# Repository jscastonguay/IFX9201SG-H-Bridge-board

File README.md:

# IFX9201SG-H-Bridge-board
HB board based on IFX9201SG IC.

This board is the replacement part of PmodHB5. This is why it follows the same interfaces

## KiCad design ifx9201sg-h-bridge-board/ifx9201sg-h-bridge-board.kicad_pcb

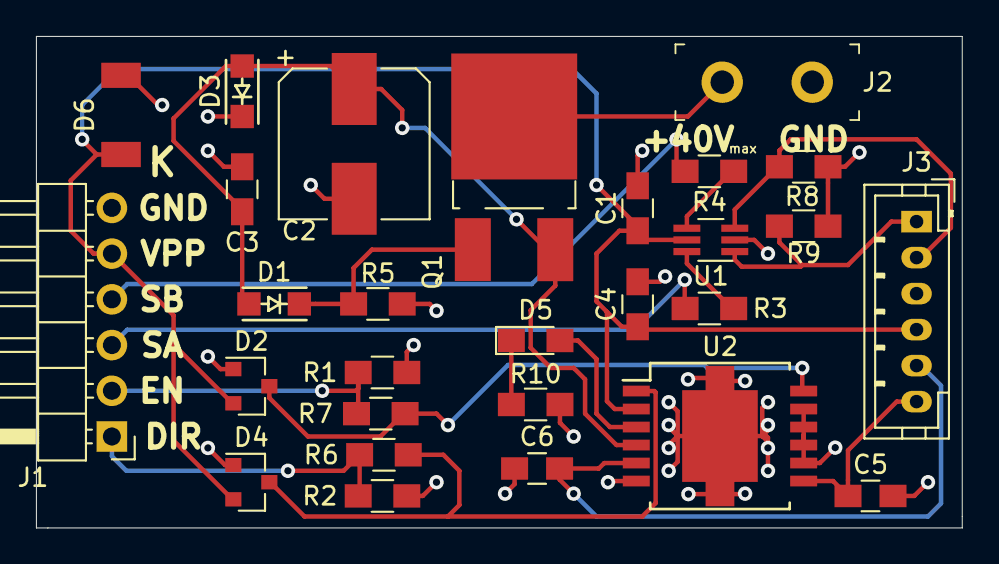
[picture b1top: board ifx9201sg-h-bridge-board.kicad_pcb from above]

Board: 2 copper layers, 51.4 x 27.3 mm, 28 parts (0 on the bottom side), 19 nets.

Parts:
C1, C3, C4: 0.1u; C_0805_HandSoldering
C2: 100u; CP_Elec_8x10
C5, C6: 10n; C_0805_HandSoldering
D1: BZT52B10; SOD-123F
D2, D4: BAT54S; SOT-23
D3: BZT52B43; SOD-123F
D5: 150080RS75000; LED_0805_HandSoldering
D6: PDZVTFTR5.1B; SOD-128
J1: Conn_01x06; Pin_Header_Angled_1x06_Pitch2.54mm
J2: 1935161; Terminal_Block_D1.3mm_P5mm
J3: S6B-PH-K-S(LF)(SN); JST_PH_B6B-PH-K_06x2.00mm_Straight
Q1: AOD407; TO-252-2_Rectifier
R1, R2, R5, R8, R9: 10k; R_0805_HandSoldering
R3, R4: 100; R_0805_HandSoldering
R6, R7: 1k; R_0805_HandSoldering
R10: 150; R_0805_HandSoldering
U1: 74LVC2G17; SOT-363_SC-70-6_Handsoldering
U2: IFX9201SG; PG-DSO-12-17

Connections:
GND: C1.2, C2.2, C3.2, C4.2, C5.2, C6.2, D2.1, D3.2, D4.1, D6.2, J1.6, J2.2, J3.3, R1.2, R2.2, R5.2, R8.2, R9.2, R10.2, U1.2, U2.6, U2.8, U2.9, U2.10, U2.11, U2.13
unnamed: C2.1, C3.1, D1.1, D3.1, Q1.3, U2.4
unnamed: C5.1, J3.6, U2.7
unnamed: C6.1, J3.5, U2.5
unnamed: D1.2, Q1.1, R5.1
unnamed: D2.3, R7.1, U2.12
unnamed: D4.3, R6.2, U2.1
unnamed: D5.1, R10.1
unnamed: D5.2, U2.3
unnamed: J1.1, R2.1, R6.1
unnamed: J1.2, R1.1, R7.2
unnamed: J1.3, R3.2
unnamed: J1.4, R4.2
unnamed: J2.1, Q1.2
unnamed: R3.1, U1.6
unnamed: R4.1, U1.4
SA_IN: J3.1, R9.1, U1.1
SB_IN: J3.2, R8.1, U1.3
VPP: C1.1, C4.1, D2.2, D4.2, D6.1, J1.5, J3.4, U1.5, U2.2

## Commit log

2019-04-14 Initial release for schematic review.
2019-04-14 Fixed minor problem.
2019-04-19 During dev. Schematic and parts association done. BOM also done.
2019-04-24 During dev: PCB done except texts.
2019-04-24 PCB completed
2019-04-29 Completed, Gerber produced.
2019-04-29 Oups, forgot to add files.
2019-04-29 Oups, add the gerber in zip file.
2019-04-29 Rename the BOM file.
